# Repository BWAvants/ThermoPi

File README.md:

# ThermoPi
Python code for Raspberry Pi based thermocouple measurement, logging, and reporting using a custom PCB with 2x MAX31855 Thermocouple reader ICs.

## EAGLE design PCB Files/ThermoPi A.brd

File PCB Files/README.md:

These files were created in Eagle Cad in May of 2018

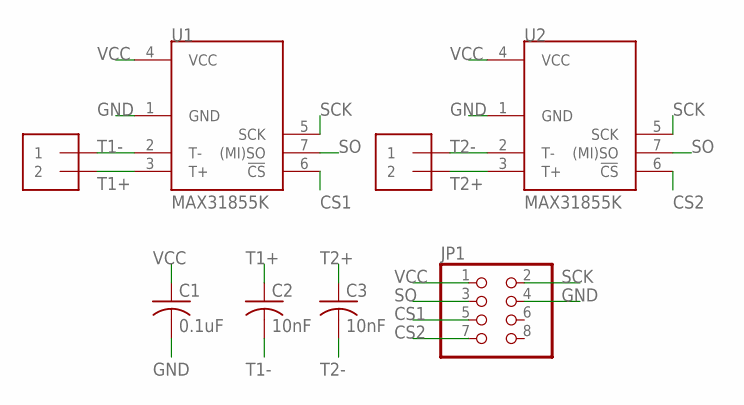
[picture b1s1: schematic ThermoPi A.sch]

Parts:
C1: 0.1uF; C0603
C2, C3: 10nF; C0603
J1, J2: 1X2-3.5MM
JP1: PINHD-2X4; 2X04
U1, U2: MAX31855K; SO08

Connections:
CS1: JP1.5, U1.6 (!CS)
CS2: JP1.7, U2.6 (!CS)
GND: C1.2, JP1.4, U1.1 (GND), U2.1 (GND)
SCK: JP1.2, U1.5 (SCK), U2.5 (SCK)
SO: JP1.3, U1.7 ((MI)SO), U2.7 ((MI)SO)
T1+: C2.1, J1.2, U1.3 (T+)
T1-: C2.2, J1.1, U1.2 (T-)
T2+: C3.1, J2.2, U2.3 (T+)
T2-: C3.2, J2.1, U2.2 (T-)
VCC: C1.1, JP1.1, U1.4 (VCC), U2.4 (VCC)

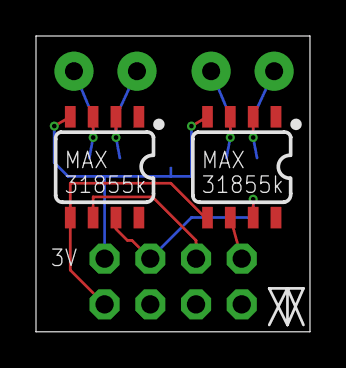
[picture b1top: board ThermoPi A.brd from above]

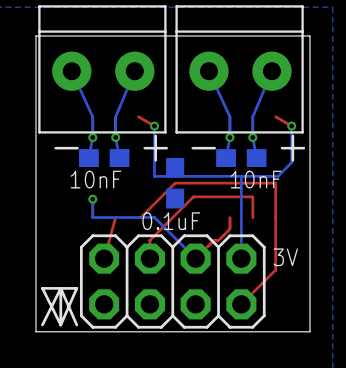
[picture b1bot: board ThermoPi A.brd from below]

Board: 2 copper layers, 15.2 x 16.4 mm, 8 parts (6 on the bottom side), 10 nets.

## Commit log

2019-06-10 Rename ThermoPi.py to Python Scripts/ThermoPi.py
2019-06-10 Rename ThermoPiMP.py to Python Scripts/ThermoPiMP.py
2019-06-10 Rename monitorThermoPi.py to Python Scripts/monitorThermoPi.py

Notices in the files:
parts and their libraries:
SparkFun-IC-Conversion: Licensing: Creative Commons ShareAlike 4.0 International - https://creativecommons.org/licenses/by-sa/4.0
